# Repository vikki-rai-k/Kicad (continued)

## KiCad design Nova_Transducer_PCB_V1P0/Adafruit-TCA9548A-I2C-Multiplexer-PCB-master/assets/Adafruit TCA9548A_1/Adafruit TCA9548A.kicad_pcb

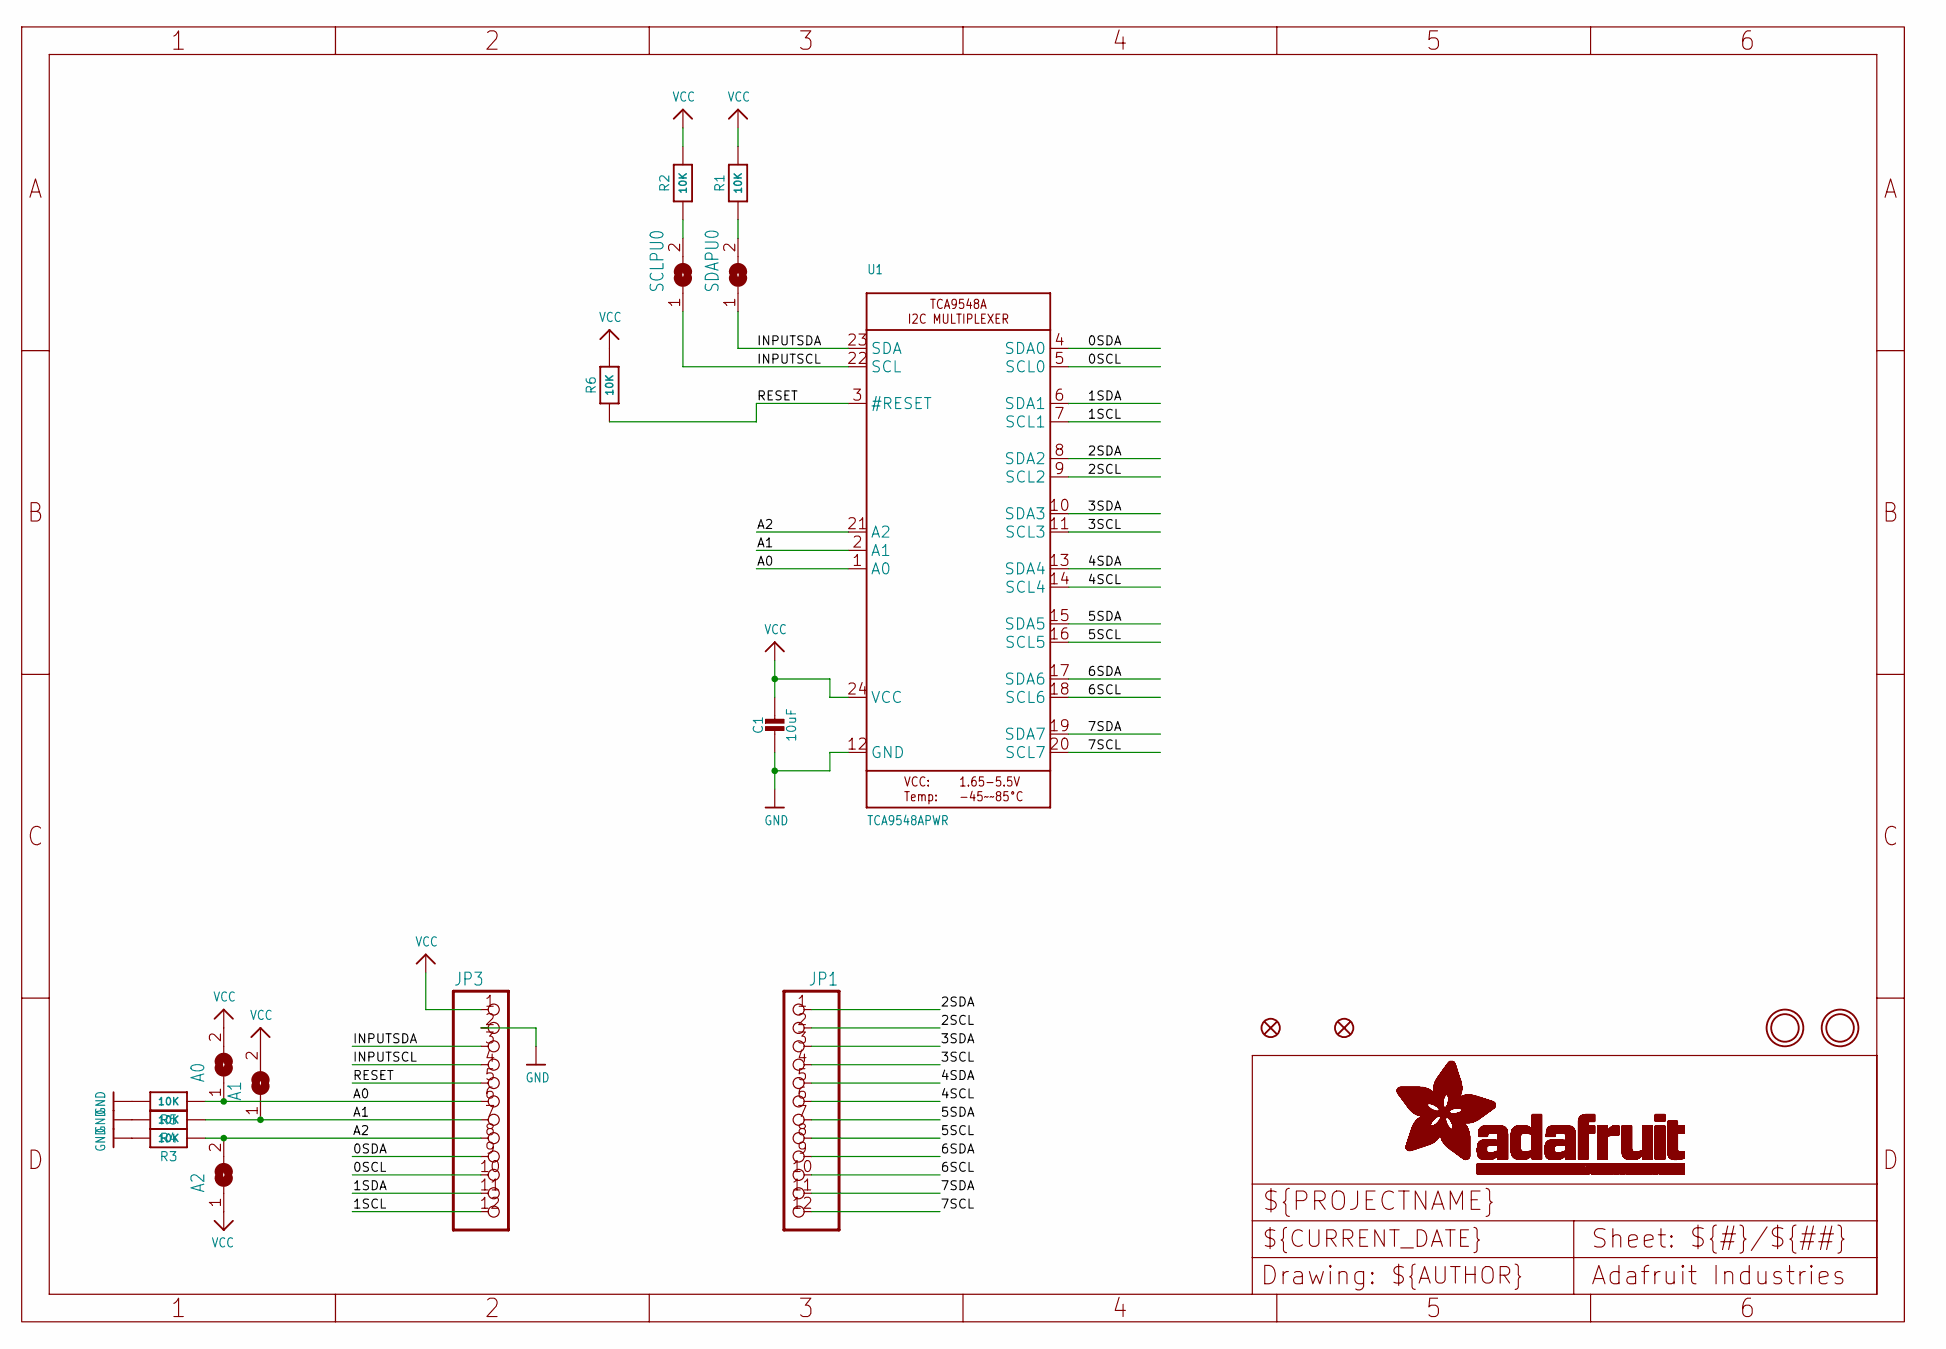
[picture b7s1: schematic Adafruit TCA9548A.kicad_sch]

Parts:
A0, A1, A2: SOLDERJUMPER; SOLDERJUMPER_ARROW_NOPASTE
C1: 10uF; 0805-NO
FID1, FID3: FIDUCIAL""; FIDUCIAL_1MM
JP1, JP3: HEADER-1X12; 1X12_ROUND
R1, R2, R3, R4, R5: 10K; 0805-NO
R6: 10K; _0805MP
SCLPU0: SOLDERJUMPERCLOSED; SOLDERJUMPER_CLOSEDWIRE
SDAPU0: SOLDERJUMPERCLOSED; SOLDERJUMPER_CLOSEDWIRE
U1: TCA9548APWR; TSSOP24
U$4, U$5: MOUNTINGHOLE2.5; MOUNTINGHOLE_2.5_PLATED

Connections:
0SCL: JP3.10, U1.5 (SCL0)
0SDA: JP3.9, U1.4 (SDA0)
1SCL: JP3.12, U1.7 (SCL1)
1SDA: JP3.11, U1.6 (SDA1)
2SCL: JP1.2, U1.9 (SCL2)
2SDA: JP1.1, U1.8 (SDA2)
3SCL: JP1.4, U1.11 (SCL3)
3SDA: JP1.3, U1.10 (SDA3)
4SCL: JP1.6, U1.14 (SCL4)
4SDA: JP1.5, U1.13 (SDA4)
5SCL: JP1.8, U1.16 (SCL5)
5SDA: JP1.7, U1.15 (SDA5)
6SCL: JP1.10, U1.18 (SCL6)
6SDA: JP1.9, U1.17 (SDA6)
7SCL: JP1.12, U1.20 (SCL7)
7SDA: JP1.11, U1.19 (SDA7)
A0: A0.1, JP3.6, R5.1, U1.1 (A0)
A1: A1.1, JP3.7, R4.1, U1.2 (A1)
A2: A2.2, JP3.8, R3.1, U1.21 (A2)
GND: C1.2, JP3.2, R3.2, R4.2, R5.2, U1.12 (GND)
INPUTSCL: JP3.4, SCLPU0.1, U1.22 (SCL)
INPUTSDA: JP3.3, SDAPU0.1, U1.23 (SDA)
unnamed: R2.1, SCLPU0.2
unnamed: R1.1, SDAPU0.2
RESET: JP3.5, R6.1, U1.3 (#RESET)
VCC: A0.2, A1.2, A2.1, C1.1, JP3.1, R1.2, R2.2, R6.2, U1.24 (VCC)

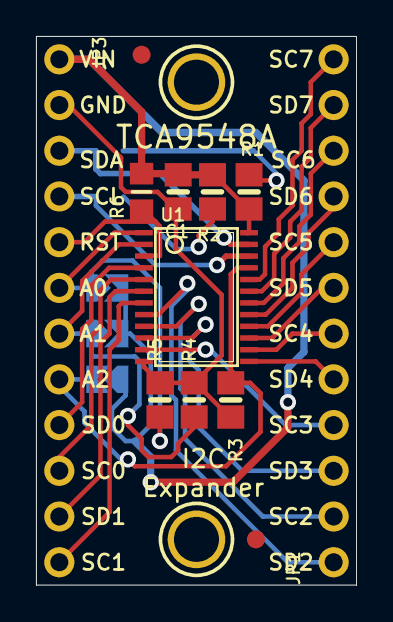
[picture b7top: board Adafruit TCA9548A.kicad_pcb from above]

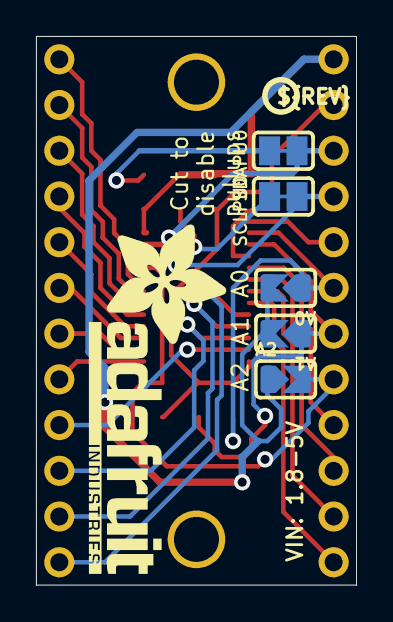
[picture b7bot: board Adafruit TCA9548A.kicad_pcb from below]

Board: 2 copper layers, 17.8 x 30.5 mm, 21 parts (7 on the bottom side), 26 nets.

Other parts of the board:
U$6: PCBFEAT-REV-040
U$7: ADAFRUIT_TEXT_20MM

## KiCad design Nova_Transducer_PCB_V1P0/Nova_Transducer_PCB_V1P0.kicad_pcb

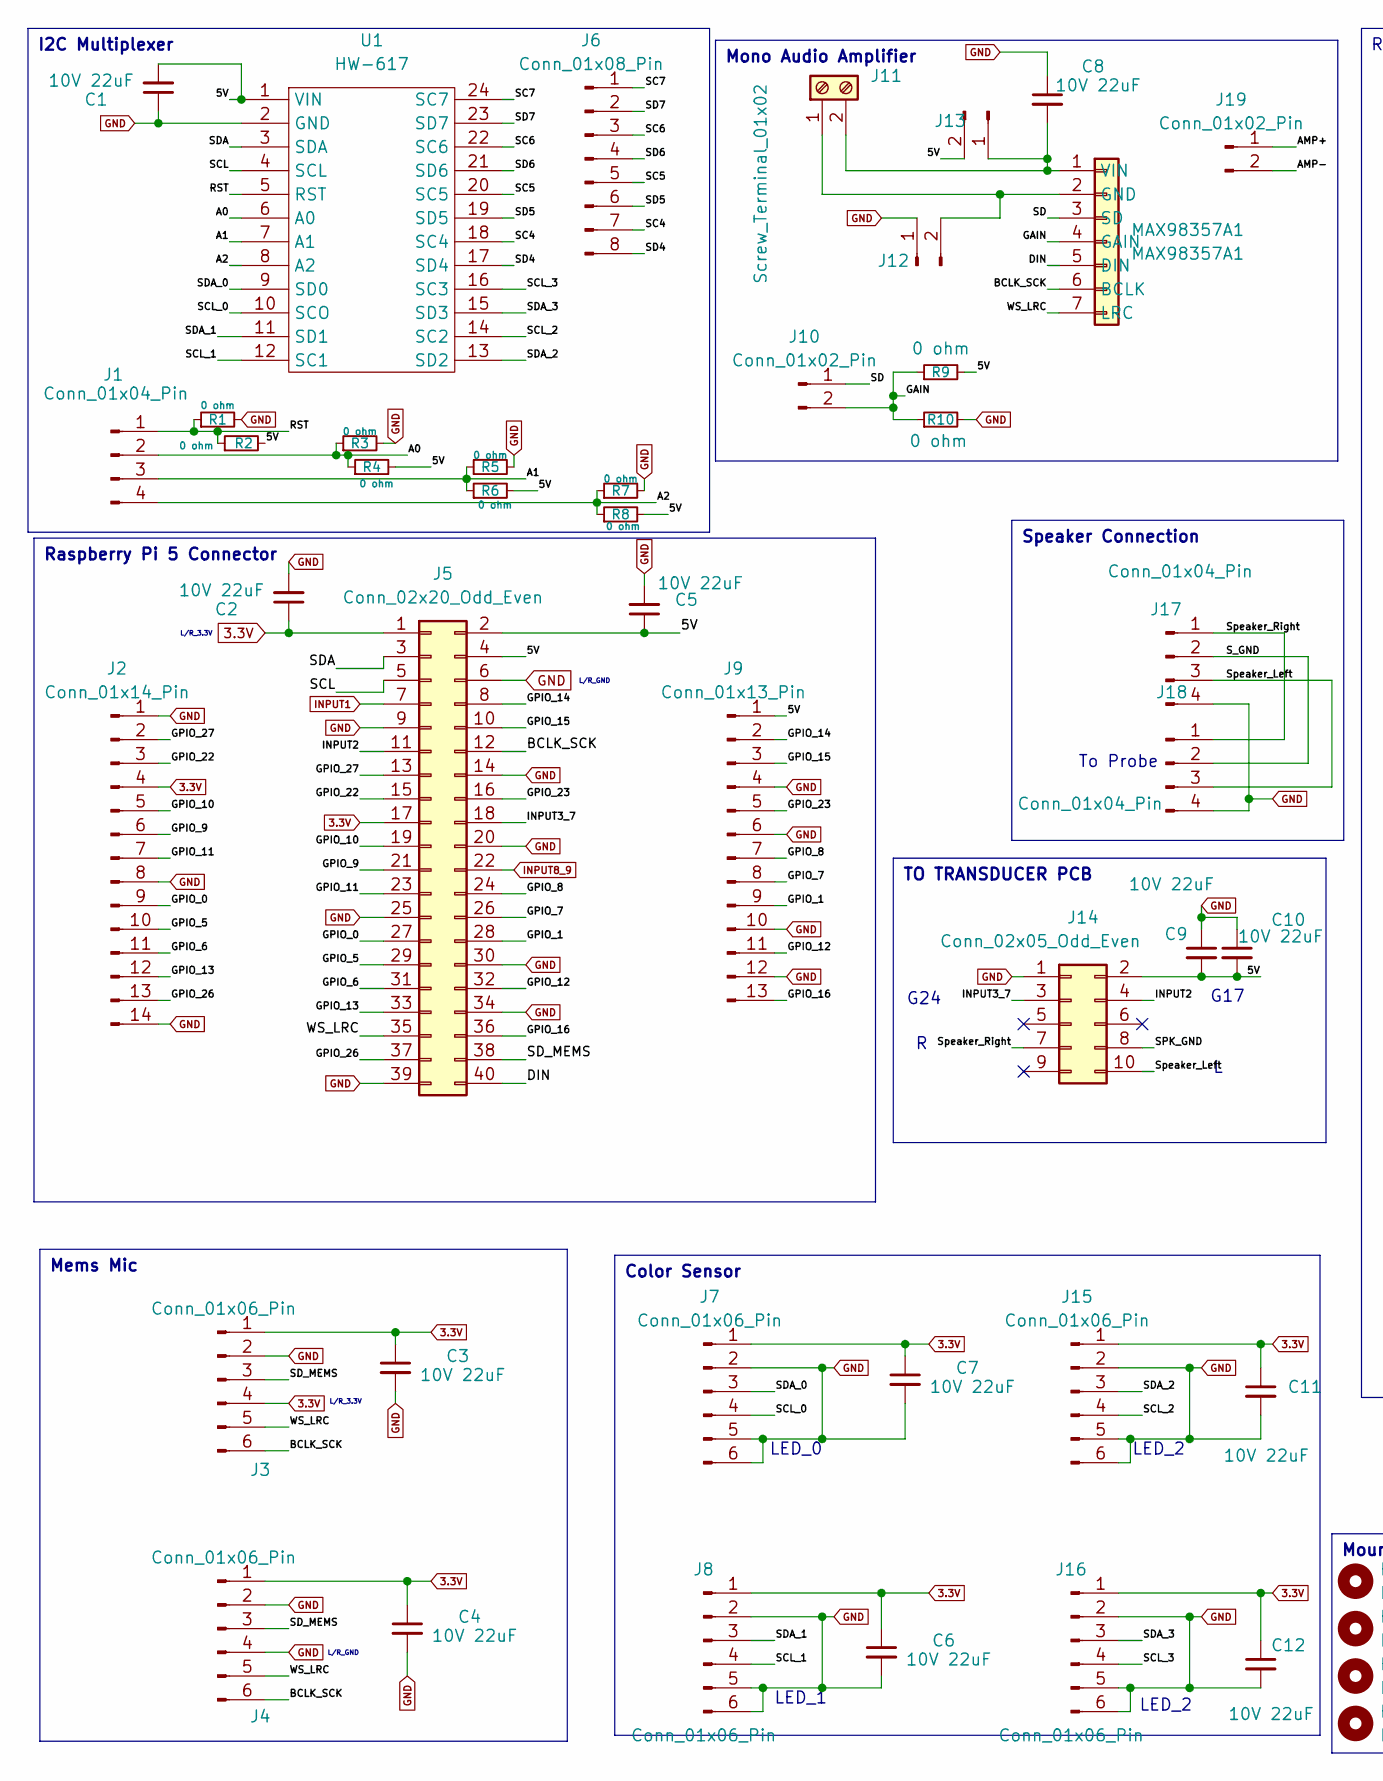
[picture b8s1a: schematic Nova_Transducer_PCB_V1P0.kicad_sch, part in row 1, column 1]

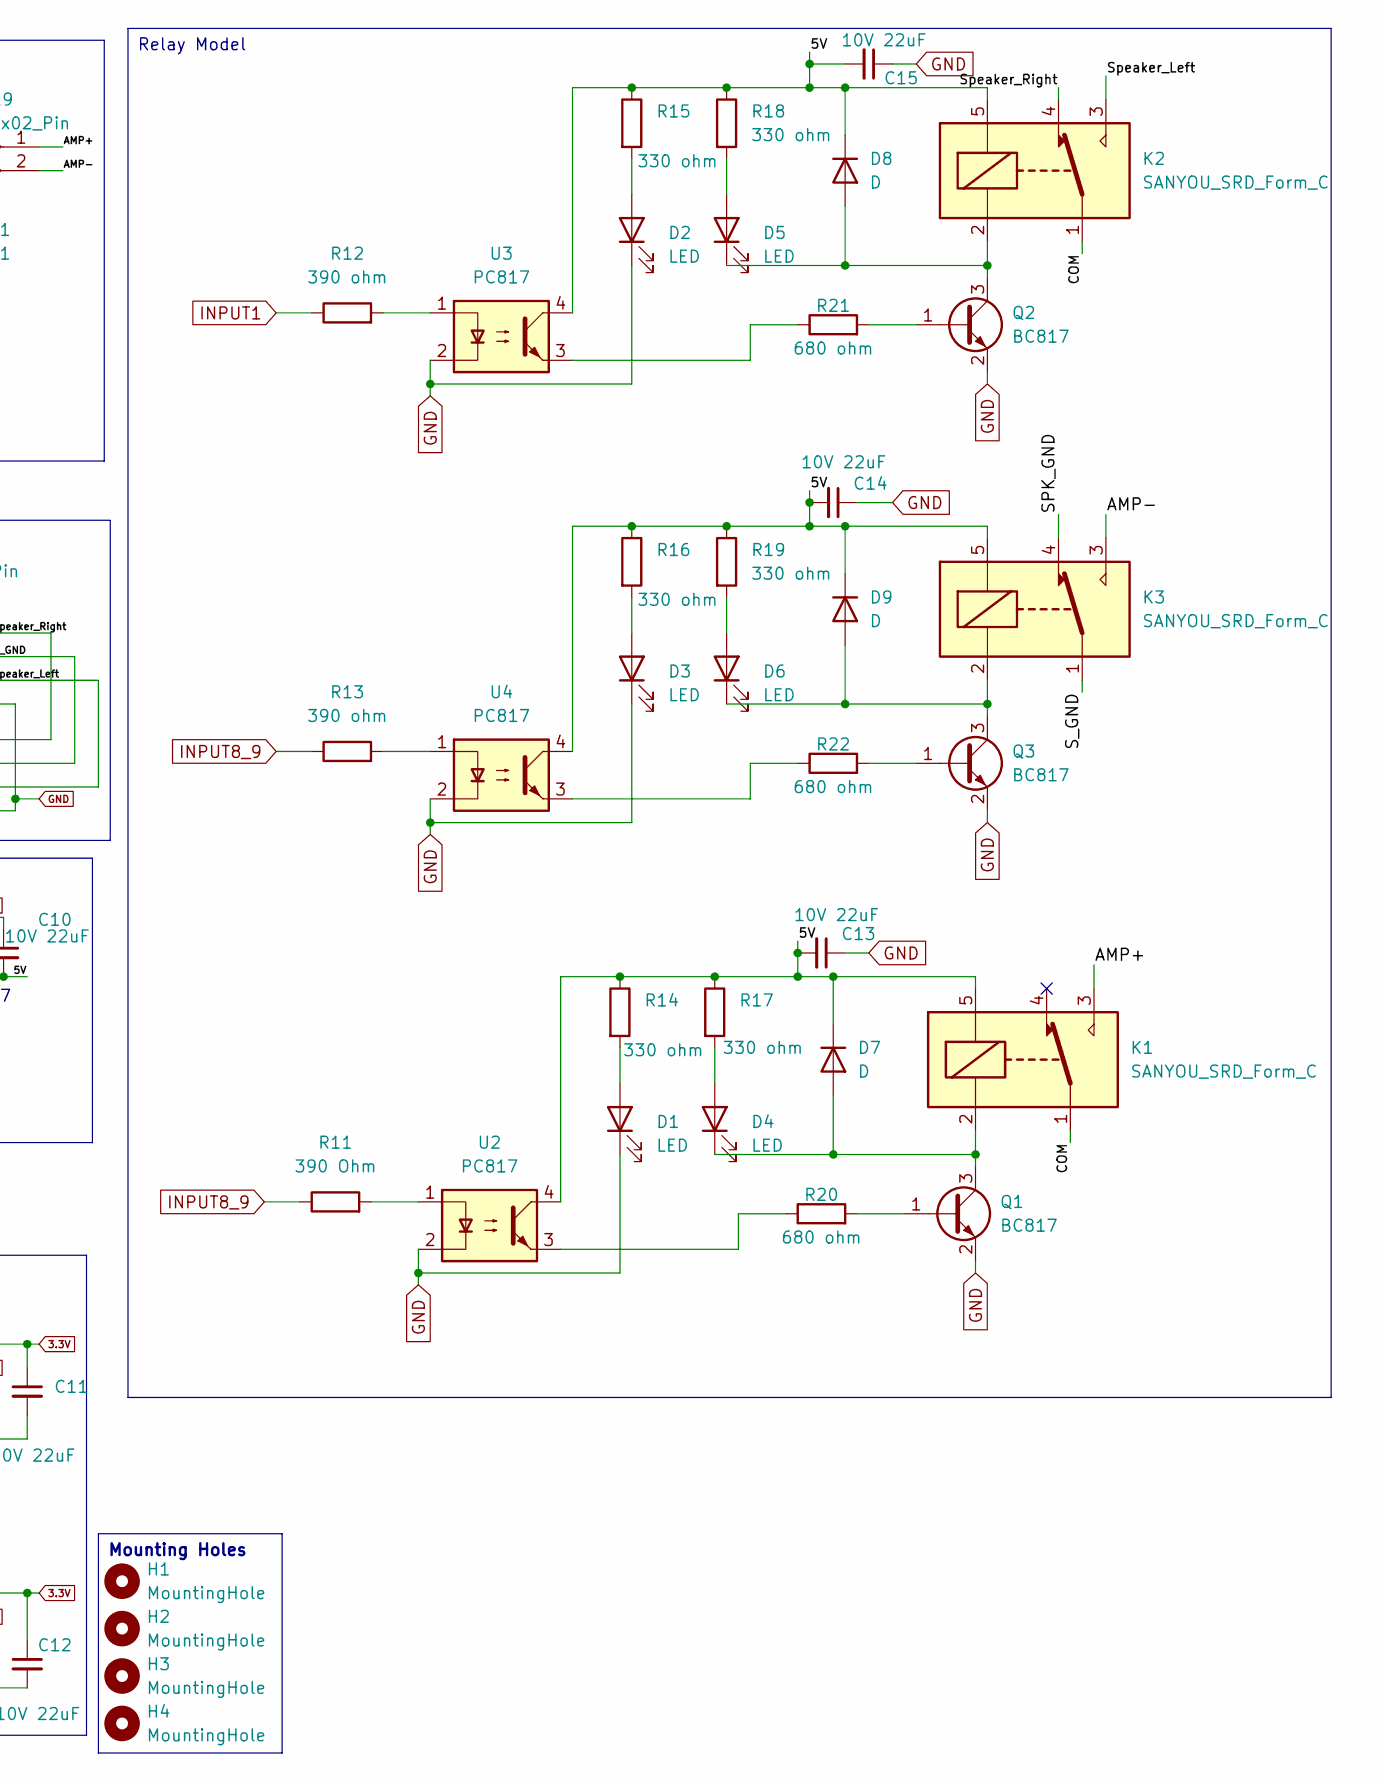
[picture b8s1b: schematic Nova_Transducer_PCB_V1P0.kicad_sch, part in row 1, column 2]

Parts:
C1, C2, C3, C4, C5, C6, C7, C8, C9, C10, C11, C12, C13, C14, C15: 10V 22uF; GRM188R61A226ME15D; mpn GRM188R61A226ME15D
D1, D2, D3, D4, D5, D6: LED; LED_0603_1608Metric; mpn 19-21SURC/S530-A3/TR8
D7, D8, D9: D; D_SOD-523; mpn RB751S40T1G
H1, H2, H3, H4: MountingHole; MountingHole_3.2mm_M3
J1, J18: Conn_01x04_Pin; PinHeader_1x04_P2.54mm_Vertical
J2: Conn_01x14_Pin; PinHeader_1x14_P2.54mm_Vertical
J3, J4, J7, J8, J15, J16: Conn_01x06_Pin; JST_EH_B6B-EH-A_1x06_P2.50mm_Vertical; mpn 6 Pin JST-XH Male Straight 2515 Connect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
J5: Conn_02x20_Odd_Even; IDC-Header_2x20_P2.54mm_Latch_Vertical; mpn 40 Pin Straight Male IDC Socket Connect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
J6: Conn_01x08_Pin; PinHeader_1x08_P2.54mm_Vertical
J9: Conn_01x13_Pin; PinHeader_1x13_P2.54mm_Vertical
J10: Conn_01x02_Pin; PinHeader_1x02_P2.54mm_Vertical
J11: Screw_Terminal_01x02; TerminalBlock_Phoenix_MKDS-1,5-2-5.08_1x02_P5.08mm_Horizont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; mpn 1888687
J12, J13: Conn_01x02_Pin; PinSocket_1x02_P2.54mm_Vertical
J14: Conn_02x05_Odd_Even; PinHeader_2x05_P2.54mm_Vertical; mpn 10 Pin Straight Male IDC Socket Connect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
J17: Conn_01x04_Pin; JST_EH_B4B-EH-A_1x04_P2.50mm_Vertical; mpn 4 Pin JST-XH Male Straight 2515 Connect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
J19: Conn_01x02_Pin; JST_EH_B2B-EH-A_1x02_P2.50mm_Vertical; mpn 2 Pin JST-XH Male Straight 2515 Connect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
K1, K2, K3: SANYOU_SRD_Form_C; Relay_SPDT_SANYOU_SRD_Series_Form_C; mpn SRD-05VDC-SL-C
MAX98357A1: MAX98357A1; MAX98357A_NEW; mpn MAX98357
Q1, Q2, Q3: BC817; SOT-23; mpn BC817
R1, R2, R3, R4, R5, R6, R7, R8, R9, R10: 0 ohm; R_0603_1608Metric; mpn WR06X000 PTL
R11: 390 Ohm; R_0603_1608Metric; mpn RC0603FR-07390RL
R12, R13: 390 ohm; R_0603_1608Metric; mpn RC0603FR-07390RL
R14, R15, R16, R17, R18, R19: 330 ohm; R_0603_1608Metric; mpn CR-03FTP-330R
R20, R21, R22: 680 ohm; R_0603_1608Metric; mpn RC0603FR-07680RL
U1: HW-617; mpn CJMCU TCA9548A
U2, U3, U4: PC817; DIP-4_W7.62mm; mpn PC817X1NSZ1B

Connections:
3.3V: C2.1, C3.1, C4.1, C6.1, C7.1, C11.1, C12.1, J2.4, J3.1, J3.4, J4.1, J5.1, J5.17, J7.1, J8.1, J15.1, J16.1
/5V: C1.2, C5.1, C9.2, C10.2, C13.2, C14.2, C15.2, D7.1 (K), D8.1 (K), D9.1 (K), J5.2, J5.4, J9.1, J13.2, J14.2, K1.5, K2.5, K3.5, R2.2, R4.2, R6.2, R8.2, R9.2, R14.1, R15.1, R16.1, R17.1, R18.1, R19.1, U1.1 (VIN), U2.4, U3.4, U4.4
/A0: J1.2, R3.1, R4.1, U1.6 (A0)
/A1: J1.3, R5.1, R6.1, U1.7 (A1)
/A2: J1.4, R7.1, R8.1, U1.8 (A2)
/AMP+: J19.1, K1.3
/AMP-: J19.2, K3.3
/BCLK_SCK: J3.6, J4.6, J5.12, MAX98357A1.6 (BCLK)
/COM: K1.1, K2.1
/DIN: J5.40, MAX98357A1.5 (DIN)
/GAIN: J10.2, MAX98357A1.4 (GAIN), R9.1, R10.1
/GPIO_0: J2.9, J5.27
/GPIO_1: J5.28, J9.9
/GPIO_5: J2.10, J5.29
/GPIO_6: J2.11, J5.31
/GPIO_7: J5.26, J9.8
/GPIO_8: J5.24, J9.7
/GPIO_9: J2.6, J5.21
/GPIO_10: J2.5, J5.19
/GPIO_11: J2.7, J5.23
/GPIO_12: J5.32, J9.11
/GPIO_13: J2.12, J5.33
/GPIO_14: J5.8, J9.2
/GPIO_15: J5.10, J9.3
/GPIO_16: J5.36, J9.13
/GPIO_22: J2.3, J5.15
/GPIO_23: J5.16, J9.5
/GPIO_26: J2.13, J5.37
/GPIO_27: J2.2, J5.13
/INPUT2: J5.11, J14.4
/INPUT3_7: J5.18, J14.3
/RST: J1.1, R1.1, R2.1, U1.5 (RST)
/SC4: J6.7, U1.18 (SC4)
/SC5: J6.5, U1.20 (SC5)
/SC6: J6.3, U1.22 (SC6)
/SC7: J6.1, U1.24 (SC7)
/SCL: J5.5, U1.4 (SCL)
/SCL_0: J7.4, U1.10 (SCO)
/SCL_1: J8.4, U1.12 (SC1)
/SCL_2: J15.4, U1.14 (SC2)
/SCL_3: J16.4, U1.16 (SC3)
/SD: J10.1, MAX98357A1.3 (SD)
/SD4: J6.8, U1.17 (SD4)
/SD5: J6.6, U1.19 (SD5)
/SD6: J6.4, U1.21 (SD6)
/SD7: J6.2, U1.23 (SD7)
/SDA: J5.3, U1.3 (SDA)
/SDA_0: J7.3, U1.9 (SD0)
/SDA_1: J8.3, U1.11 (SD1)
/SDA_2: J15.3, U1.13 (SD2)
/SDA_3: J16.3, U1.15 (SD3)
/SD_MEMS: J3.3, J4.3, J5.38
/SPK_GND: J14.8, K3.4
/S_GND: J17.2, J18.2, K3.1
/Speaker_Left: J14.10, J17.3, J18.3, K2.3
/Speaker_Right: J14.7, J17.1, J18.1, K2.4
/WS_LRC: J3.5, J4.5, J5.35, MAX98357A1.7 (LRC)
GND: C1.1, C2.2, C3.2, C4.2, C5.2, C6.2, C7.2, C8.1, C9.1, C10.1, C11.2, C12.2, C13.1, C14.1, C15.1, D1.1 (K), D2.1 (K), D3.1 (K), J2.1, J2.8, J2.14, J3.2, J4.2, J4.4, J5.6, J5.9, J5.14, J5.20, J5.25, J5.30, J5.34, J5.39, J7.2, J7.5, J7.6, J8.2, J8.5, J8.6, J9.4, J9.6, J9.10, J9.12, J12.1, J14.1, J15.2, J15.5, J15.6, J16.2, J16.5, J16.6, J17.4, J18.4, Q1.2 (E), Q2.2 (E), Q3.2 (E), R1.2, R3.2, R5.2, R7.2, R10.2, U1.2 (GND), U2.2, U3.2, U4.2
INPUT1: J5.7, R12.1
INPUT8_9: J5.22, R11.1, R13.1
unnamed: D1.2 (A), R14.2
unnamed: D2.2 (A), R15.2
unnamed: D3.2 (A), R16.2
unnamed: D4.2 (A), R17.2
unnamed: D4.1 (K), D7.2 (A), K1.2, Q1.3 (C)
unnamed: D5.2 (A), R18.2
unnamed: D5.1 (K), D8.2 (A), K2.2, Q2.3 (C)
unnamed: D6.2 (A), R19.2
unnamed: D6.1 (K), D9.2 (A), K3.2, Q3.3 (C)
unnamed: J11.1, J12.2, MAX98357A1.2 (GND)
unnamed: C8.2, J11.2, J13.1, MAX98357A1.1 (VIN)
unnamed: Q1.1 (B), R20.2
unnamed: Q2.1 (B), R21.2
unnamed: Q3.1 (B), R22.2
unnamed: R11.2, U2.1
unnamed: R12.2, U3.1
unnamed: R13.2, U4.1
unnamed: R20.1, U2.3
unnamed: R21.1, U3.3
unnamed: R22.1, U4.3

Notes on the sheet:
LED_2
L/R_3.3V
L/R_GND
G17
LED_0
G24
To Probe
LED_1
Raspberry Pi 5 Connector
Color Sensor
Mems Mic
Relay Model
I2C Multiplexer
Mono Audio Amplifier
Speaker Connection
TO TRANSDUCER PCB
Mounting Holes

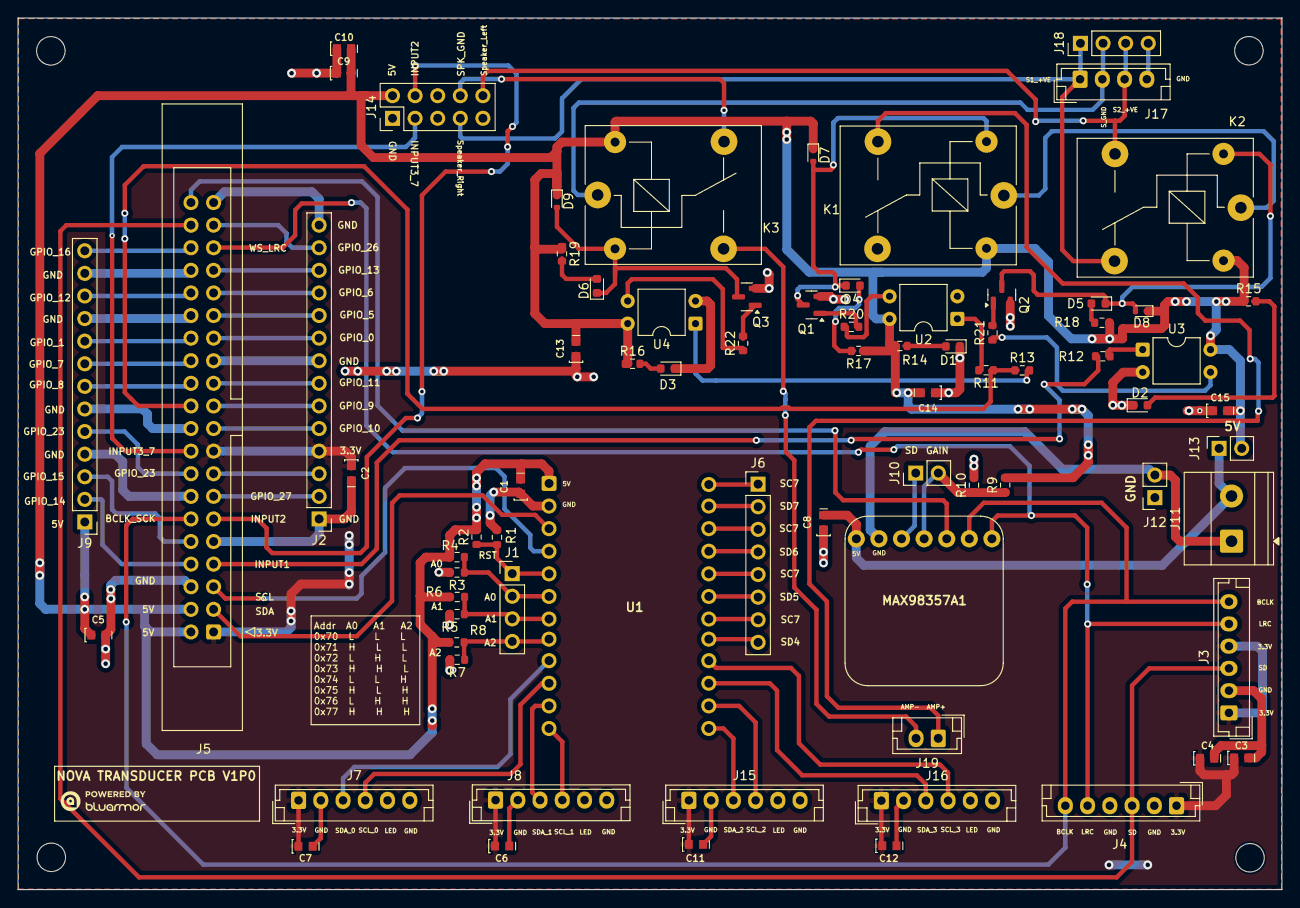
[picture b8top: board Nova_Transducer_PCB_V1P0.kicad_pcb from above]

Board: 2 copper layers, 142.1 x 98.0 mm, 80 parts (0 on the bottom side), 80 nets.

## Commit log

2026-05-02 "Pushing some PCB files"
2026-05-02 File Renamed as ABLIB
2026-05-05 Removed Halo_3_v1p1 project
2026-05-05 Removed LIB
2026-05-05 Removed Kicad lib
2026-06-29 "Update"
